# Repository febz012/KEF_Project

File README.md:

# KEF_Project
This repository consists of a series of IoT projects with LoRA

# 1)  Weather Station 
      A weather station constructed using Industrial grade sensors. 
      The data is collected periodically and transmitted to a capture station using LoRa.
      After the data is received at the capture station using a gateway,it is uploaded to the cloud using a Nodemcu/Raspberry Pi
      
      The following sensor data were collected
      *****************************************
      
      i)    Humidity and Temperature
      ii)   Wind Speed
      iii)  Wind Direction
      iv)   Rain Gauge
      v)    Barometric Pressure
      vi)   Dew Point
      vii)  Air Density
      
      Components used
      ****************
      
      i)    Atmega328P
      ii)   Nodemcu/Raspberry Pi
      iii)  SMD Resistors,Capacitors
      iv)   Max485 TTL Converter Module
      v)    CD4053 triple 2-channel MUX/DEMUX
      vi)   RF Module E32-868T30D
      vii)  Weather Station Sensors (Detailed list provided in repo)

# 2) LIDAR WATER LEVEL MEASURING UNIT
      Measure Water level of a well using Lidar and transmit the data to a capture station via LoRa.
      The data is then uploaded to a Cloud Storage and made availble on Internet.
      
      LIDAR WATER LEVEL MEASURING UNIT
      Measure Water level of a well using Lidar and transmit the data to a capture station via LoRa.
      The data is then uploaded to a Cloud Storage and made availble on Internet.

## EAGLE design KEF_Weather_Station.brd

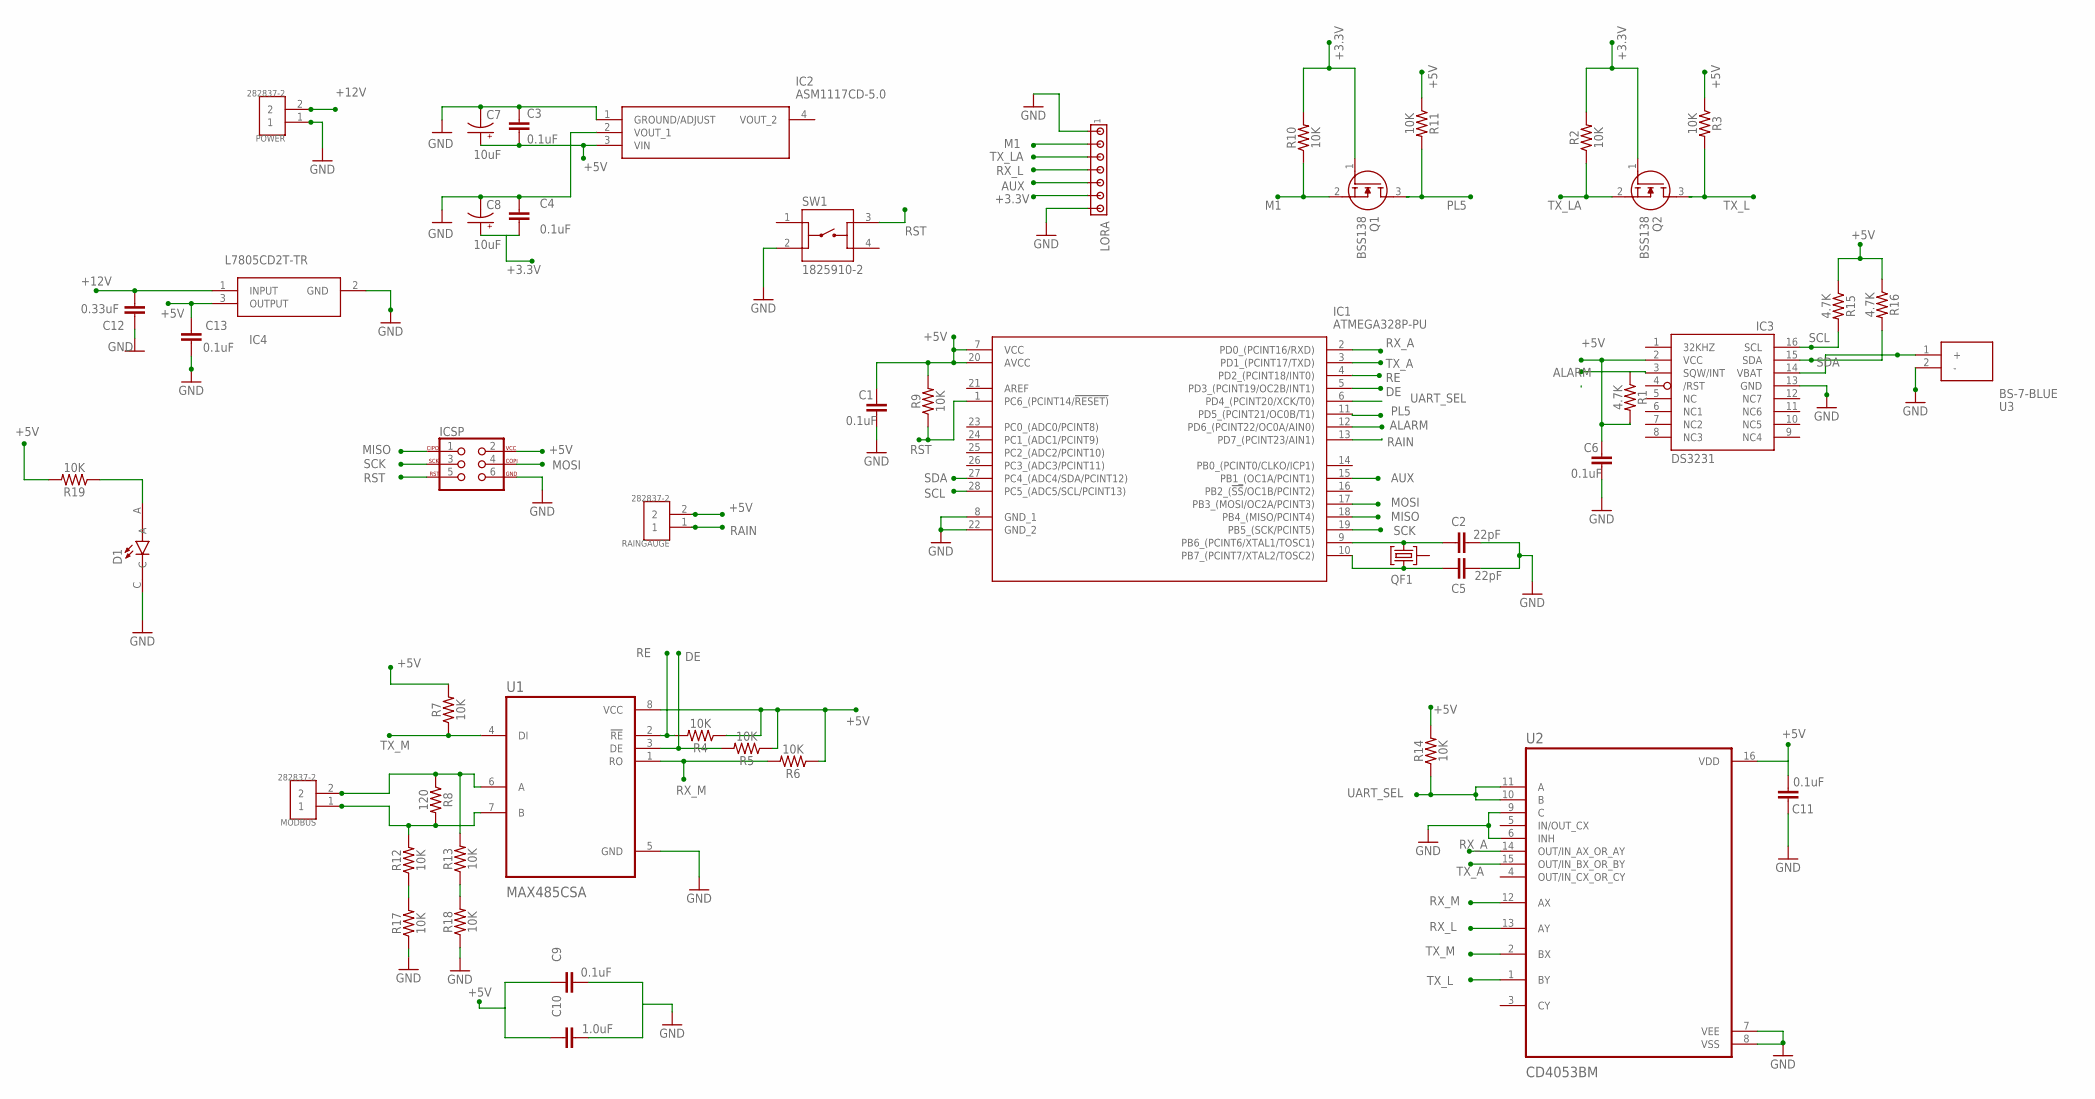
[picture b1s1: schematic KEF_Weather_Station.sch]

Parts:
C1, C3, C4, C6, C9, C11, C13: 0.1uF; 1206
C2, C5: 22pF; 1206
C7, C8: 10uF; EIA3216
C10: 1.0uF; 1206
C12: 0.33uF; 1206
D1: LTST-C230KFKT; LEDC3216X110
IC1: ATMEGA328P-PU; DIP794W53P254L3467H457Q28N
IC2: ASM1117CD-5.0; SOT229P700X180-4N
IC3: DS3231/SO; SO16W
IC4: L7805CD2T-TR; L7805CD2T
ICSP: AVR_SPI_PROG_3X2NS; 2X3-NS
LORA: MTA07-100; 10X07MTA
MODBUS: 282837-2; TE_282837-2
POWER: 282837-2; TE_282837-2
Q1, Q2: BSS138; SOT95P240X120-3N
QF1: 8M10AHC49T; HC49U
R1, R15, R16: 4.7K; 1206
R2, R3, R4, R5, R6, R7, R9, R10, R11, R12, R13, R14, R17, R18, R19: 10K; 1206
R8: 120; 1206
RAINGAUGE: 282837-2; TE_282837-2
SW1: 1825910-2; TE_1825910-2
U1: MAX485CSA; SOIC127P600X175-8N
U2: CD4053BM; SOIC127P600X175-16N
U3: BS-7-BLUE; BS-7-BLUE_1

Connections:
+3.3V: C4.2, C8.+, LORA.6, Q1.1 (G), Q2.1 (G), R2.2, R10.2
+5V: C1.1, C3.2, C6.1, C7.+, C9.1, C10.1, C11.2, C13.1, IC1.7 (VCC), IC1.20 (AVCC), IC2.3 (VIN), IC3.2 (VCC), IC4.3 (OUTPUT), ICSP.2, R1.2, R3.1, R4.1, R5.1, R6.1, R7.2, R9.2, R11.1, R14.2, R15.1, R16.1, R19.2, RAINGAUGE.2, U1.8 (VCC), U2.16 (VDD)
+12V: C12.1, IC4.1 (INPUT), POWER.2
ALARM: IC1.12 (PD6_(PCINT22/OC0A/AIN0)), IC3.3 (SQW/INT), R1.1
AUX: IC1.15 (PB1_(OC1A/PCINT1)), LORA.5
DE: IC1.5 (PD3_(PCINT19/OC2B/INT1)), R5.2, U1.3 (DE)
GND: C1.2, C2.2, C3.1, C4.1, C5.2, C6.2, C7.-, C8.-, C9.2, C10.2, C11.1, C12.2, C13.2, D1.C, IC1.8 (GND_1), IC1.22 (GND_2), IC2.1 (GROUND/ADJUST), IC2.2 (VOUT_1), IC3.13 (GND), IC4.2 (GND), ICSP.6, LORA.1, LORA.7, POWER.1, R17.1, R18.1, SW1.2, U1.5 (GND), U2.6 (INH), U2.7 (VEE), U2.8 (VSS), U2.9 (C), U3.2 (-)
M1: LORA.2, Q1.2 (S), R10.1
MISO: IC1.18 (PB4_(MISO/PCINT4)), ICSP.1
MOSI: IC1.17 (PB3_(MOSI/OC2A/PCINT3)), ICSP.4
unnamed: R12.1, R17.2
unnamed: IC3.14 (VBAT), U3.1 (+)
unnamed: C5.1, IC1.10 (PB7_(PCINT7/XTAL2/TOSC2)), QF1.1
unnamed: C2.1, IC1.9 (PB6_(PCINT6/XTAL1/TOSC1)), QF1.3
unnamed: R13.1, R18.2
unnamed: D1.A, R19.1
unnamed: MODBUS.1, R8.2, R12.2, U1.7 (B)
unnamed: MODBUS.2, R8.1, R13.2, U1.6 (A)
PL5: IC1.11 (PD5_(PCINT21/OC0B/T1)), Q1.3 (D), R11.2
RAIN: IC1.13 (PD7_(PCINT23/AIN1)), RAINGAUGE.1
RE: IC1.4 (PD2_(PCINT18/INT0)), R4.2, U1.2 (!RE)
RST: IC1.1 (PC6_(PCINT14/!RESET)), ICSP.5, R9.1, SW1.3
RX_A: IC1.2 (PD0_(PCINT16/RXD)), U2.14 (OUT/IN_AX_OR_AY)
RX_L: LORA.4, U2.13 (AY)
RX_M: R6.2, U1.1 (RO), U2.12 (AX)
SCK: IC1.19 (PB5_(SCK/PCINT5)), ICSP.3
SCL: IC1.28 (PC5_(ADC5/SCL/PCINT13)), IC3.16 (SCL), R15.2
SDA: IC1.27 (PC4_(ADC4/SDA/PCINT12)), IC3.15 (SDA), R16.2
TX_A: IC1.3 (PD1_(PCINT17/TXD)), U2.15 (OUT/IN_BX_OR_BY)
TX_L: Q2.3 (D), R3.2, U2.1 (BY)
TX_LA: LORA.3, Q2.2 (S), R2.1
TX_M: R7.1, U1.4 (DI), U2.2 (BX)
UART_SEL: IC1.6 (PD4_(PCINT20/XCK/T0)), R14.1, U2.10 (B), U2.11 (A)

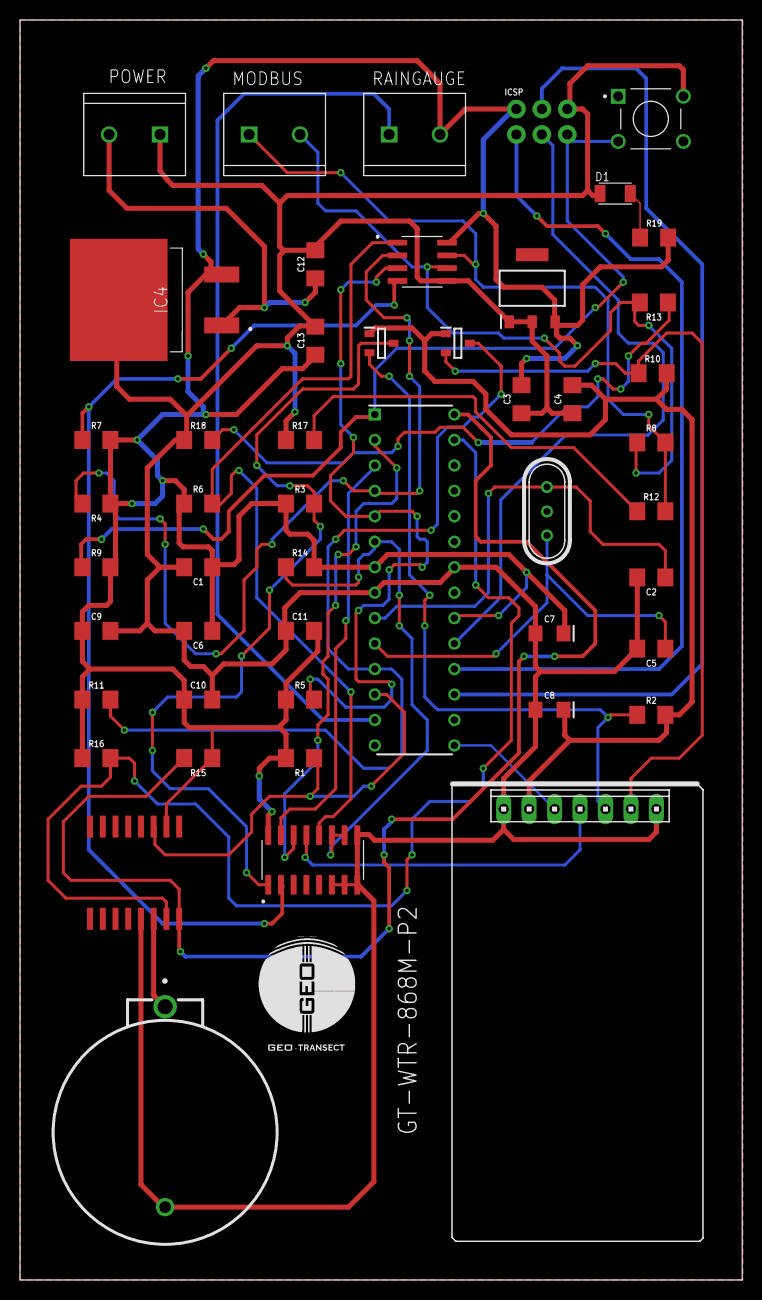
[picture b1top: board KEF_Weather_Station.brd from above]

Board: 2 copper layers, 72.1 x 125.7 mm, 49 parts (0 on the bottom side), 33 nets.

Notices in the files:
parts and their libraries:
SparkFun-Capacitors: Licensing: Creative Commons ShareAlike 4.0 International - https://creativecommons.org/licenses/by-sa/4.0
